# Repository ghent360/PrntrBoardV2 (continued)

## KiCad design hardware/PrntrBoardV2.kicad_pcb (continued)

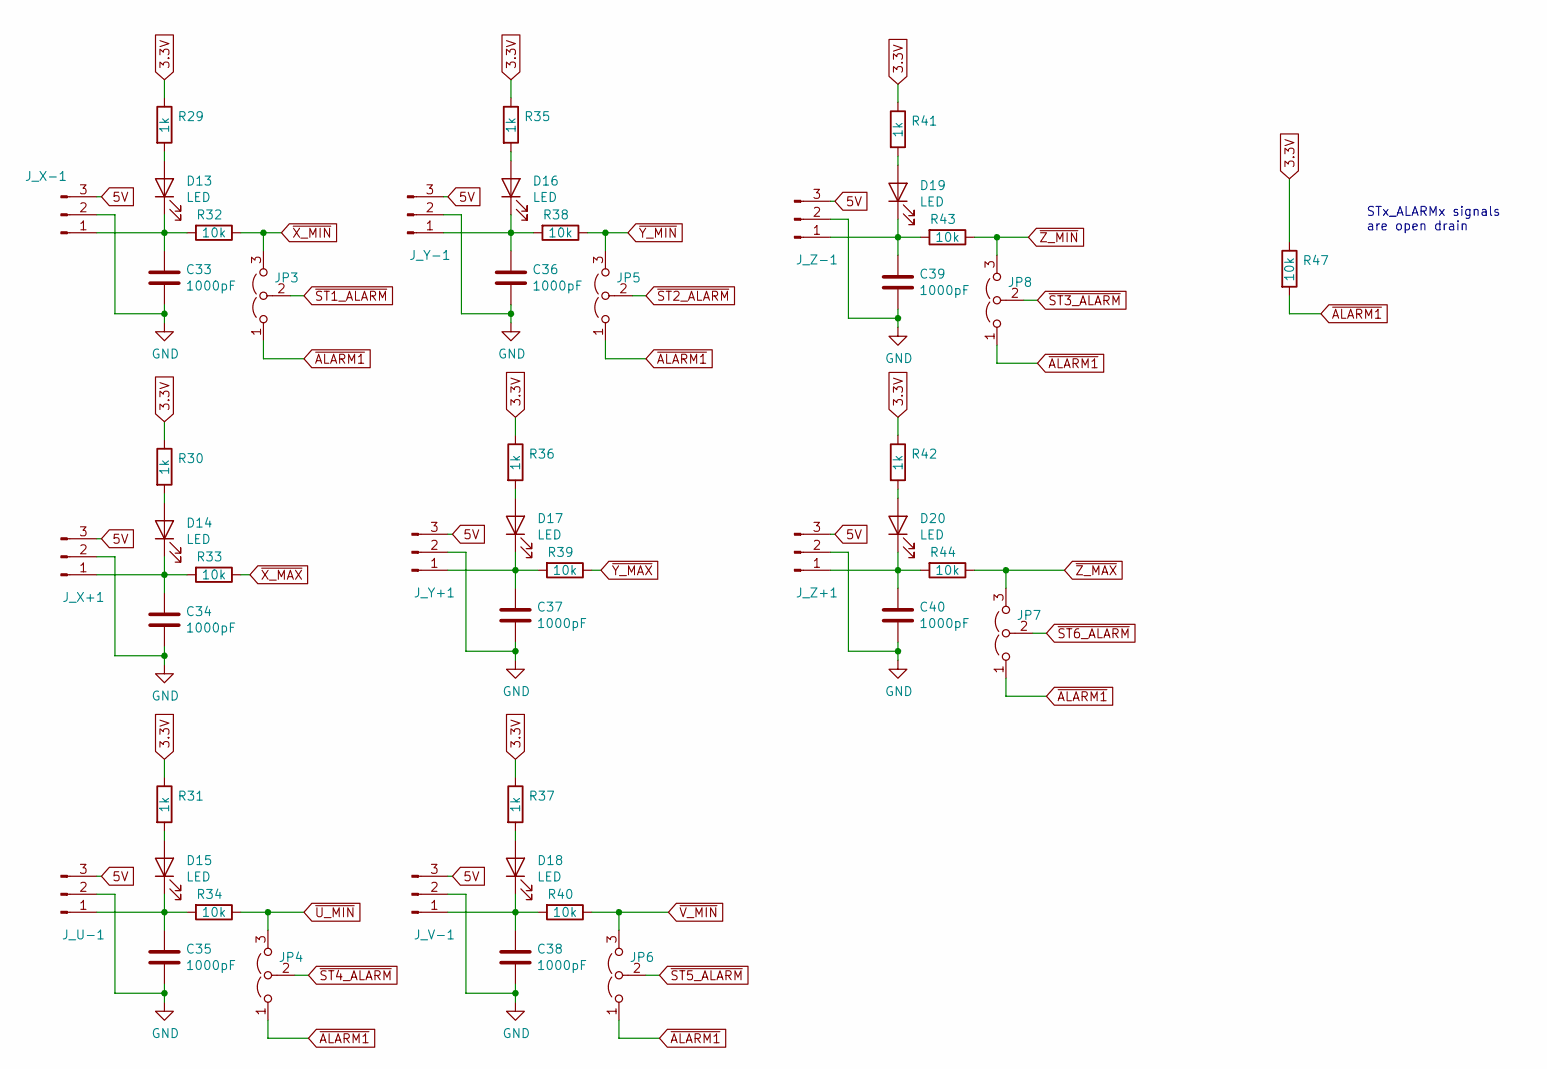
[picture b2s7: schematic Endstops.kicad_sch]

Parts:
C33, C34, C35, C36, C37, C38, C39, C40: 1000pF; C_0603_1608Metric; Part # CL10B102KB8NNNC; LCSC Part # C1588
D13, D14, D15, D16, D17, D18, D19, D20: LED; LED_0603_1608Metric; Part # KT-0603R; LCSC Part # C2286
JP3, JP4, JP5, JP6, JP7, JP8: Jumper_3_Open; PinHeader_1x03_P2.54mm_Vertical; LCSC Part # C152153
J_U-1: JST XH 3p; JST_XH_B3B-XH-A_1x03_P2.50mm_Vertical
J_V-1: JST XH 3p; JST_XH_B3B-XH-A_1x03_P2.50mm_Vertical
J_X+1: JST XH 3p; JST_XH_B3B-XH-A_1x03_P2.50mm_Vertical
J_X-1: JST XH 3p; JST_XH_B3B-XH-A_1x03_P2.50mm_Vertical
J_Y+1: JST XH 3p; JST_XH_B3B-XH-A_1x03_P2.50mm_Vertical
J_Y-1: JST XH 3p; JST_XH_B3B-XH-A_1x03_P2.50mm_Vertical
J_Z+1: JST XH 3p; JST_XH_B3B-XH-A_1x03_P2.50mm_Vertical
J_Z-1: JST XH 3p; JST_XH_B3B-XH-A_1x03_P2.50mm_Vertical
R29, R30, R31, R35, R36, R37, R41, R42: 1k; R_0603_1608Metric; Part # 0603WAF1001T5E; LCSC Part # C21190
R32, R33, R34, R38, R39, R40, R43, R44, R47: 10k; R_0603_1608Metric; Part # 0603WAF1002T5E; LCSC Part # C25804

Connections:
3.3V: R29.1, R30.1, R31.1, R35.1, R36.1, R37.1, R41.1, R42.1, R47.1; also elsewhere on the board
5V: J_U-1.3, J_V-1.3, J_X+1.3, J_X-1.3, J_Y+1.3, J_Y-1.3, J_Z+1.3, J_Z-1.3; also elsewhere on the board
GND: C33.2, C34.2, C35.2, C36.2, C37.2, C38.2, C39.2, C40.2, J_U-1.2, J_V-1.2, J_X+1.2, J_X-1.2, J_Y+1.2, J_Y-1.2, J_Z+1.2, J_Z-1.2; also elsewhere on the board
unnamed: C33.1, D13.1 (K), J_X-1.1, R32.2
unnamed: C34.1, D14.1 (K), J_X+1.1, R33.2
unnamed: C35.1, D15.1 (K), J_U-1.1, R34.2
unnamed: C36.1, D16.1 (K), J_Y-1.1, R38.2
unnamed: C37.1, D17.1 (K), J_Y+1.1, R39.2
unnamed: C38.1, D18.1 (K), J_V-1.1, R40.2
unnamed: C39.1, D19.1 (K), J_Z-1.1, R43.2
unnamed: C40.1, D20.1 (K), J_Z+1.1, R44.2
unnamed: D13.2 (A), R29.2
unnamed: D14.2 (A), R30.2
unnamed: D15.2 (A), R31.2
unnamed: D16.2 (A), R35.2
unnamed: D17.2 (A), R36.2
unnamed: D18.2 (A), R37.2
unnamed: D19.2 (A), R41.2
unnamed: D20.2 (A), R42.2
~ALARM1: JP3.1 (A), JP4.1 (A), JP5.1 (A), JP6.1 (A), JP7.1 (A), JP8.1 (A), R47.2; also elsewhere on the board
~ST1_ALARM: JP3.2 (C); also elsewhere on the board
~ST2_ALARM: JP5.2 (C); also elsewhere on the board
~ST3_ALARM: JP8.2 (C); also elsewhere on the board
~ST4_ALARM: JP4.2 (C); also elsewhere on the board
~ST5_ALARM: JP6.2 (C); also elsewhere on the board
~ST6_ALARM: JP7.2 (C); also elsewhere on the board
~U_MIN: JP4.3 (B), R34.1; also elsewhere on the board
~V_MIN: JP6.3 (B), R40.1; also elsewhere on the board
~X_MAX: R33.1; also elsewhere on the board
~X_MIN: JP3.3 (B), R32.1; also elsewhere on the board
~Y_MAX: R39.1; also elsewhere on the board
~Y_MIN: JP5.3 (B), R38.1; also elsewhere on the board
~Z_MAX: JP7.3 (B), R44.1; also elsewhere on the board
~Z_MIN: JP8.3 (B), R43.1; also elsewhere on the board

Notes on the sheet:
STx_ALARMx signals are open drain

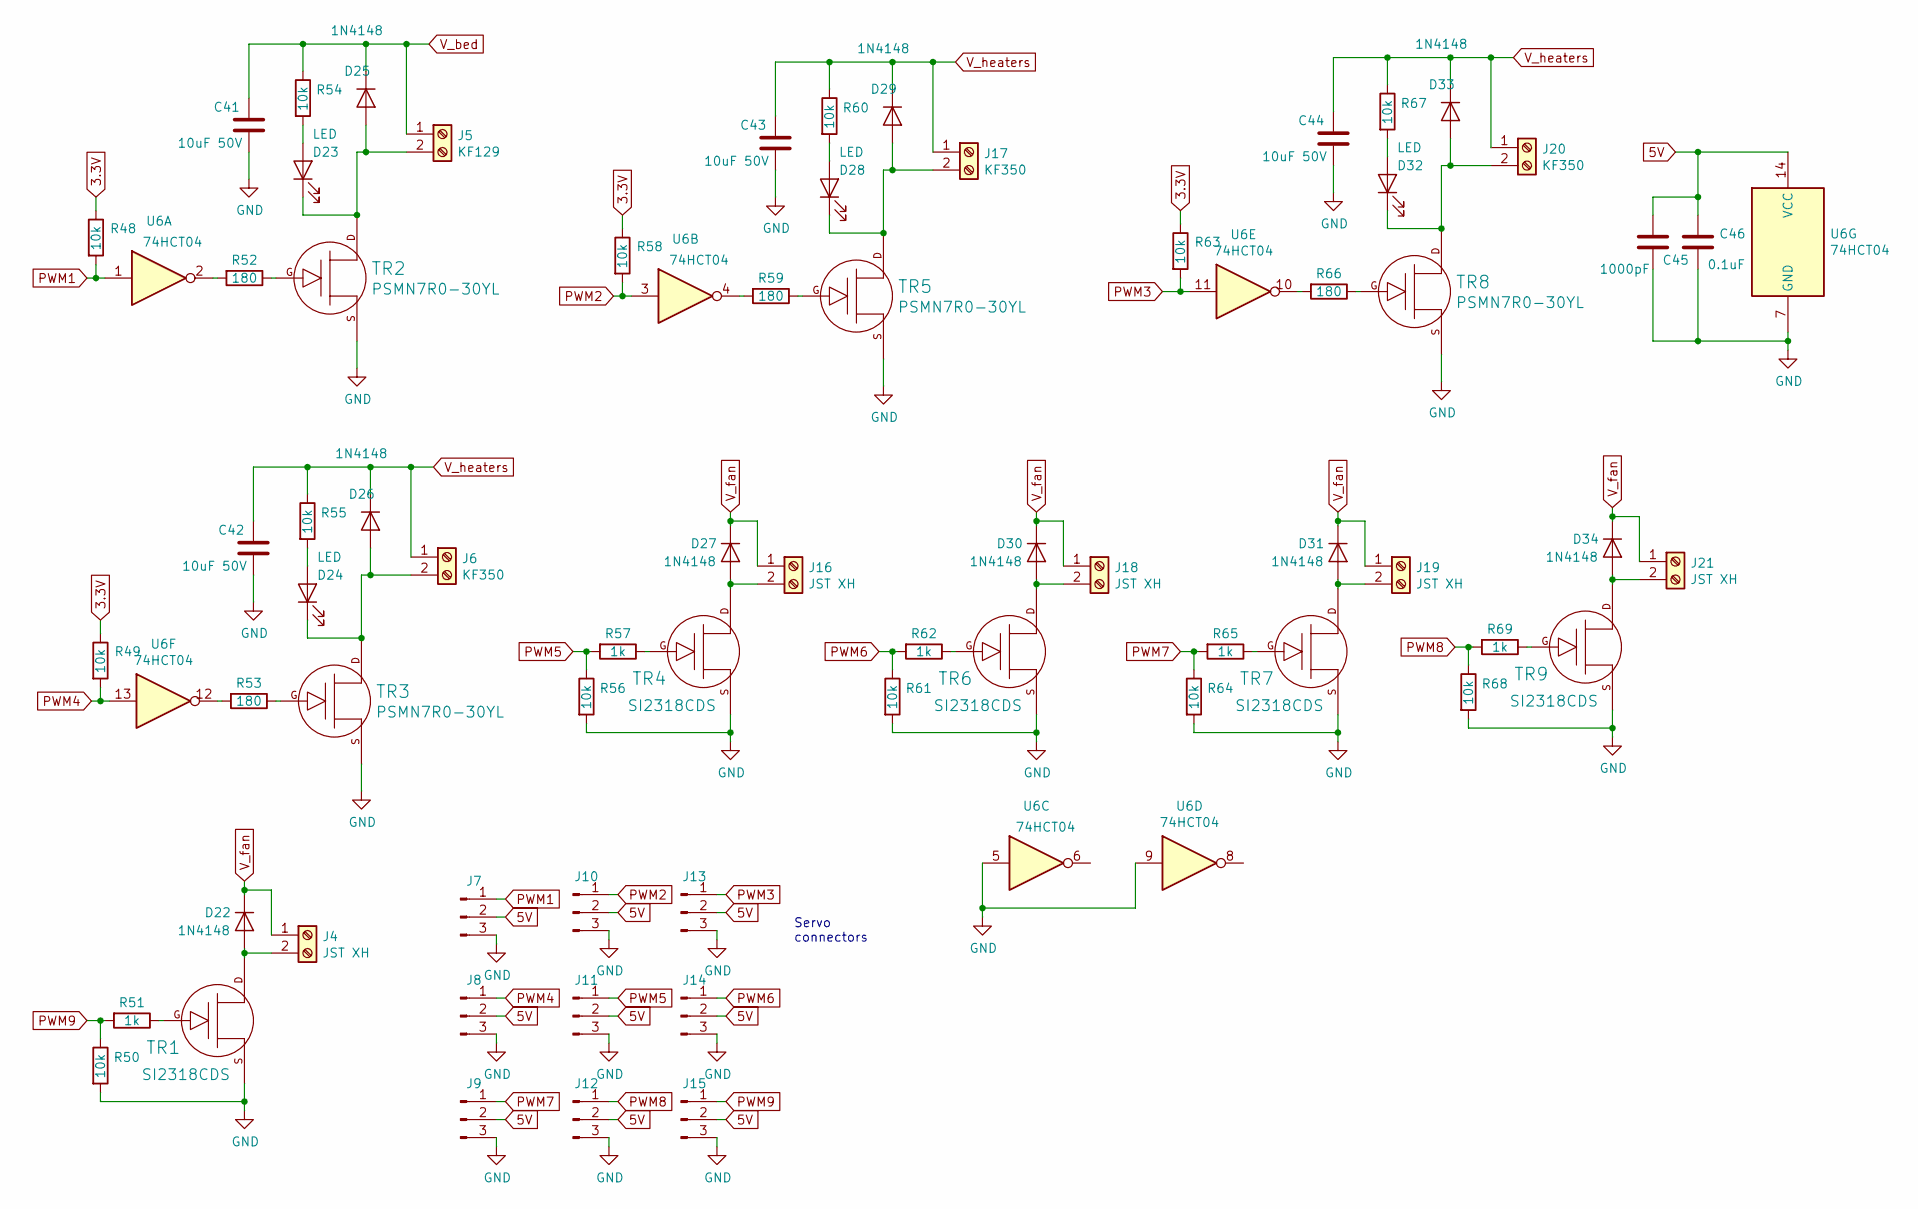
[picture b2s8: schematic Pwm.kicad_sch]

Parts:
C41, C42, C43, C44: 10uF 50V; C_1206_3216Metric; Part # CL31A106KBHNNNE; LCSC Part # C13585
C45: 1000pF; C_0603_1608Metric; Part # CL10B102KB8NNNC; LCSC Part # C1588
C46: 0.1uF; C_0603_1608Metric; Part # CC0603KRX7R9BB104; LCSC Part # C14663
D22, D25, D26, D27, D29, D30, D31, D33, D34: 1N4148; D_SOD-323_HandSoldering; Part # 1N4148WS; LCSC Part # C2128
D23, D24, D28, D32: LED; LED_0603_1608Metric; Part # KT-0603R; LCSC Part # C2286
J4, J16, J18, J19, J21: JST XH; JST_XH_B2B-XH-A_1x02_P2.50mm_Vertical
J5: KF129; TerminalBlock_Phoenix_MKDS-1,5-2-5.08_1x02_P5.08mm_Horizont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
J6, J17, J20: KF350; TerminalBlock_Phoenix_PT-1,5-2-3.5-H_1x02_P3.50mm_Horizontal
J7, J8, J9, J10, J11, J12, J13, J14, J15: Conn_01x03_Male; PinHeader_1x03_P2.54mm_Vertical
R48, R49, R50, R54, R55, R56, R58, R60, R61, R63, R64, R67, R68: 10k; R_0603_1608Metric; Part # 0603WAF1002T5E; LCSC Part # C25804
R51, R57, R62, R65, R69: 1k; R_0603_1608Metric; Part # 0603WAF1001T5E; LCSC Part # C21190
R52, R53, R59, R66: 180; R_0603_1608Metric; Part # 0603WAF1800T5E; LCSC Part # C22828
TR1, TR4, TR6, TR7, TR9: SI2318CDS; SOT-23; Part # AO3400A; LCSC Part # C20917
TR2, TR3, TR5, TR8: PSMN7R0-30YL; SOT-669_LFPAK; Part # PSMN1R5-30YLC; LCSC Part # C427523
U6: 74HCT04; TSSOP-14_4.4x5mm_P0.65mm; Part # 74HCT04PW,118; LCSC Part # C131317

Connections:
3.3V: R48.1, R49.1, R58.1, R63.1; also elsewhere on the board
5V: C45.1, C46.1, J7.2, J8.2, J9.2, J10.2, J11.2, J12.2, J13.2, J14.2, J15.2, U6.14 (VCC); also elsewhere on the board
GND: C41.2, C42.2, C43.2, C44.2, C45.2, C46.2, J7.3, J8.3, J9.3, J10.3, J11.3, J12.3, J13.3, J14.3, J15.3, R50.2, R56.2, R61.2, R64.2, R68.2, TR1.S, TR2.S, TR3.S, TR4.S, TR5.S, TR6.S, TR7.S, TR8.S, TR9.S, U6.5, U6.7 (GND), U6.9; also elsewhere on the board
unnamed: D22.2 (A), J4.2, TR1.D
unnamed: D23.1 (K), D25.2 (A), J5.2, TR2.D
unnamed: D23.2 (A), R54.2
unnamed: D24.1 (K), D26.2 (A), J6.2, TR3.D
unnamed: D24.2 (A), R55.2
unnamed: D27.2 (A), J16.2, TR4.D
unnamed: D28.1 (K), D29.2 (A), J17.2, TR5.D
unnamed: D28.2 (A), R60.2
unnamed: D30.2 (A), J18.2, TR6.D
unnamed: D31.2 (A), J19.2, TR7.D
unnamed: D32.1 (K), D33.2 (A), J20.2, TR8.D
unnamed: D32.2 (A), R67.2
unnamed: D34.2 (A), J21.2, TR9.D
unnamed: R51.1, TR1.G
unnamed: R52.1, TR2.G
unnamed: R52.2, U6.2
unnamed: R53.1, TR3.G
unnamed: R53.2, U6.12
unnamed: R57.1, TR4.G
unnamed: R59.1, TR5.G
unnamed: R59.2, U6.4
unnamed: R62.1, TR6.G
unnamed: R65.1, TR7.G
unnamed: R66.1, TR8.G
unnamed: R66.2, U6.10
unnamed: R69.1, TR9.G
PWM1: J7.1, R48.2, U6.1; also elsewhere on the board
PWM2: J10.1, R58.2, U6.3; also elsewhere on the board
PWM3: J13.1, R63.2, U6.11; also elsewhere on the board
PWM4: J8.1, R49.2, U6.13; also elsewhere on the board
PWM5: J11.1, R56.1, R57.2; also elsewhere on the board
PWM6: J14.1, R61.1, R62.2; also elsewhere on the board
PWM7: J9.1, R64.1, R65.2; also elsewhere on the board
PWM8: J12.1, R68.1, R69.2; also elsewhere on the board
PWM9: J15.1, R50.1, R51.2; also elsewhere on the board
V_bed: C41.1, D25.1 (K), J5.1, R54.1; also elsewhere on the board
V_fan: D22.1 (K), D27.1 (K), D30.1 (K), D31.1 (K), D34.1 (K), J4.1, J16.1, J18.1, J19.1, J21.1; also elsewhere on the board
V_heaters: C42.1, C43.1, C44.1, D26.1 (K), D29.1 (K), D33.1 (K), J6.1, J17.1, J20.1, R55.1, R60.1, R67.1; also elsewhere on the board

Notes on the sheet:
Servo connectors

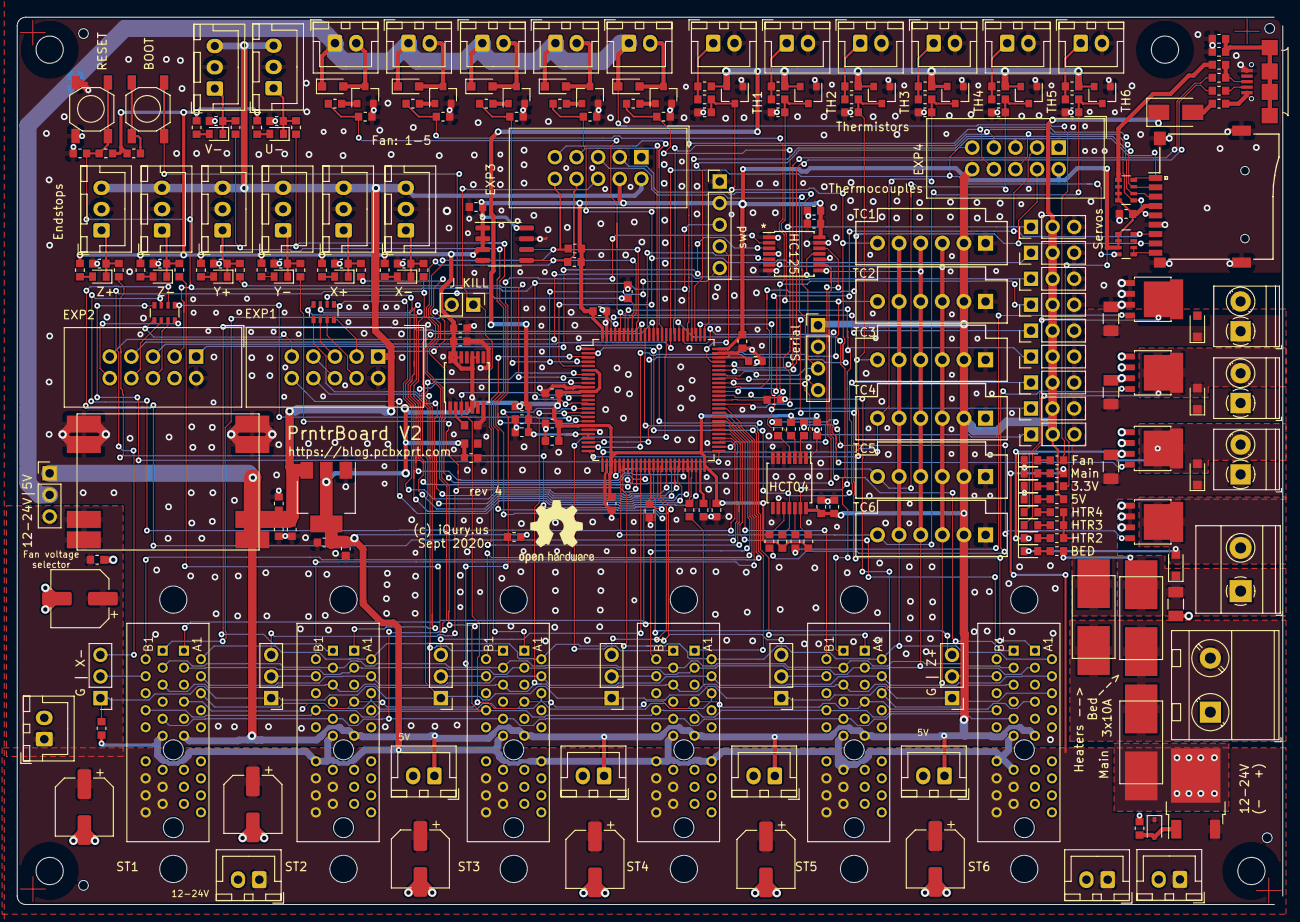
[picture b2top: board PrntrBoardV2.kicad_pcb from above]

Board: 2 copper layers, 148.7 x 104.3 mm, 266 parts (0 on the bottom side), 177 nets.

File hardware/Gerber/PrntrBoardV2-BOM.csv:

Comment,Designator,Footprint,LCSC, LCSC Part #, Part #
"10uF","C20,C23,C26,C56,C2,C5,C6,C15","PrntrBoardV2:C_0603_1608Metric","","C19702","CL10A106KP8NNNC"
"0.1uF","C21,C22,C57,C18,C19,C54,C1,C4,C7,C8,C9,C10,C11,C12,C13,C14,C17,C53,C46","PrntrBoardV2:C_0603_1608Metric","","C14663","CC0603KRX7R9BB104"
"0.1uF 50V","C24","PrntrBoardV2:C_0603_1608Metric","","C14663","CL05B104KO5NNNCC0603KRX7R9BB104C"
"100uF 35V","C25,C47,C48,C49,C50,C51,C52","Capacitor_SMD:CP_Elec_6.3x7.7","","C134792","VES101M1VTR-0607"
"1000pF","C27,C28,C29,C30,C31,C32,C33,C34,C35,C36,C37,C38,C39,C40,C3,C16,C45","PrntrBoardV2:C_0603_1608Metric","","C1588","CL10B102KB8NNNC"
"10uF 50V","C41,C42,C43,C44","PrntrBoardV2:C_1206_3216Metric","","C13585","CL31A106KBHNNNE"
"B5819W","D1,D21,D22,D25,D26,D27,D29,D30,D31,D33","Diode_SMD:D_SOD-123",""," C8598","B5819W"
"LED","D2,D3,D4,D5,D13,D14,D15,D16,D17,D18,D19,D20,D23,D24,D28,D32","PrntrBoardV2:LED_0603_1608Metric","","C2286","KT-0603R"
"10V","D6","Diode_SMD:D_SOD-323","","C131828","LM3Z10VT1G"
"BAT54S","D7,D8,D9,D10,D11,D12","Package_TO_SOT_SMD:SOT-23","","C181201","BAT54S"
"IDC 2x5","EXP1,EXP2,EXP3","Connector_IDC:IDC-Header_2x05_P2.54mm_Vertical","","C5661",""
"500mA","F1","PrntrBoardV2:R_0603_1608Metric","","C261937","TLC-FSMD050"
"Fuse","F2,F3,F4","PrntrBoardV2:2410_FuseFolder",""
"600 ohm @ 100MHz","FB1","Inductor_SMD:L_0805_2012Metric","","C1017","GZ2012D601TF"
"JST XH","J1,J2,J22,J23,J24,J25,J26,J27,J_TH1,J_TH2,J_TH3,J_TH4,J_TH5,J_TH6,J4,J16,J18,J19,J21","Connector_JST:JST_XH_B2B-XH-A_1x02_P2.50mm_Vertical",""
"KF350","J28,J6,J17,J20","PrntrBoardV2:TerminalBlock_Phoenix_PT-1,5-2-3.5-H_1x02_P3.50mm_Horizontal",""
"RJ12_Shielded","J29","Connector_RJ:RJ12_Amphenol_54601",""
"USB_B_Micro","J3","PrntrBoardV2:MC-101C","","C183609","SOFNG MC-101C"
"KF129","J5","PrntrBoardV2:TerminalBlock_Phoenix_MKDS-1,5-2-5.08_1x02_P5.08mm_Horizontal",""
"Conn_01x03_Male","J7,J8,J9,J10,J11,J12,J13,J14,J15","Connector_PinHeader_2.54mm:PinHeader_1x03_P2.54mm_Vertical",""
"Jumper_2_Open","JP1","Connector_PinHeader_2.54mm:PinHeader_1x02_P2.54mm_Vertical","","C160332",""
"Jumper_3_Open","JP2,JP3,JP4,JP5,JP6,JP7,JP8","Connector_PinHeader_2.54mm:PinHeader_1x03_P2.54mm_Vertical","","C152153",""
"Serial 0","J_SER1","Connector_PinHeader_2.54mm:PinHeader_1x04_P2.54mm_Vertical","","C358686",""
"PCIe_Stepper","J_ST1,J_ST2,J_ST3,J_ST4,J_ST5,J_ST6","PrntrBoardV2:AMPHENOL_10018784-10210TLF",""
"SWD","J_SWD1","Connector_PinHeader_2.54mm:PinHeader_1x05_P2.54mm_Vertical",""
"JST XH 3p","J_U-1,J_V-1,J_X+1,J_X-1,J_Y+1,J_Y-1,J_Z+1,J_Z-1","Connector_JST:JST_XH_B3B-XH-A_1x03_P2.50mm_Vertical",""
"KF635","J_power_in1","TerminalBlock_MetzConnect:TerminalBlock_MetzConnect_Type701_RT11L02HGLU_1x02_P6.35mm_Horizontal",""
"Net-Tie_2","NT1","NetTie:NetTie-2_SMD_Pad0.5mm",""
"NCE40P40K","Q1","Package_TO_SOT_SMD:TO-252-2","","C130100","NCE40P40K"
"22","R10,R11,R72","PrntrBoardV2:R_0603_1608Metric","","C23345","0603WAF220JT5E"
"10k","R13,R14,R19,R20,R23,R24,R27,R28,R2,R73,R77,R78,R32,R33,R34,R38,R39,R40,R43,R44,R47,R1,R3,R5,R6,R7,R70,R48,R49,R50,R54,R55,R56,R58,R60,R61,R63,R64,R67,R68","PrntrBoardV2:R_0603_1608Metric","","C25804","0603WAF1002T5E"
"470","R15,R45,R46","PrntrBoardV2:R_0603_1608Metric","","C23179","0603WAF4700T5E"
"1k","R16,R29,R30,R31,R35,R36,R37,R41,R42,R8,R51,R57,R62,R65,R69","PrntrBoardV2:R_0603_1608Metric","","C21190","0603WAF1001T5E"
"4k7","R17,R18,R21,R22,R25,R26","PrntrBoardV2:R_0603_1608Metric","","C23162","0603WAF4701T5E"
"180","R52,R53,R59,R66","PrntrBoardV2:R_0603_1608Metric","","C22828","0603WAF1800T5E"
"100k","R71,R12","PrntrBoardV2:R_0603_1608Metric","","C25803","0603WAF1003T5E"
"56","R74,R75","PrntrBoardV2:R_0603_1608Metric","","C25196","0603WAF560JT5E"
"1.5k","R9","PrntrBoardV2:R_0603_1608Metric","","C22843","0603WAF1501T5E"
"4x470","RN1,RN2","Resistor_SMD:R_Array_Convex_4x0603","","C25510","4D03WGJ0471T5E"
"4x10k","RN3","Resistor_SMD:R_Array_Convex_4x0603","","C29718","4D03WGJ0103T5E"
"SW_Push","SW_BOOT1,SW_RST1","PrntrBoardV2:Button_4x4","","C318884","TS-1187A-B-A-B"
"TC","TC1,TC2,TC3,TC4,TC5,TC6","kicad-molex-sl-footprints:Molex-SL-6POS",""
"SI2318CDS","TR1,TR4,TR6,TR7,TR9","PrntrBoardV2:SOT-23","","C20917","AO3400A"
"PSMN7R0-30YL","TR2,TR3,TR5,TR8","PrntrBoardV2:SOT-669_LFPAK","","C427523","PSMN1R5-30YLC"
"74LVC125","U1,U7","Package_SO:TSSOP-14_4.4x5mm_P0.65mm","","C6059","74LVC125APW,118"
"STM32F407VETx","U2","Package_QFP:LQFP-100_14x14mm_P0.5mm","","C28730","STM32F407VET6"
"24LC64","U3","Package_SO:SO-8_3.9x4.9mm_P1.27mm","","C5460","24LC64T-I/SN"
"AMS1117-3.3","U4","Package_TO_SOT_SMD:SOT-223-3_TabPin2","","C6186","AMS1117-3.3"
"74HCT04","U6","Package_SO:TSSOP-14_4.4x5mm_P0.65mm","","C131317","74HCT04PW,118"
"TJA1040","U8","Package_SO:SOIC-8_3.9x4.9mm_P1.27mm","","C6951","TJA1040T/CM,118"
"12MHz","X1","Oscillator:Oscillator_SMD_EuroQuartz_XO32-4Pin_3.2x2.5mm","","C29752","SIT1602AI-22-33E-12.000000D"
"MicroSD","XS1","PrntrBoardV2:Conn_uSDcard","","C111196","SOFNG TF-15×15"

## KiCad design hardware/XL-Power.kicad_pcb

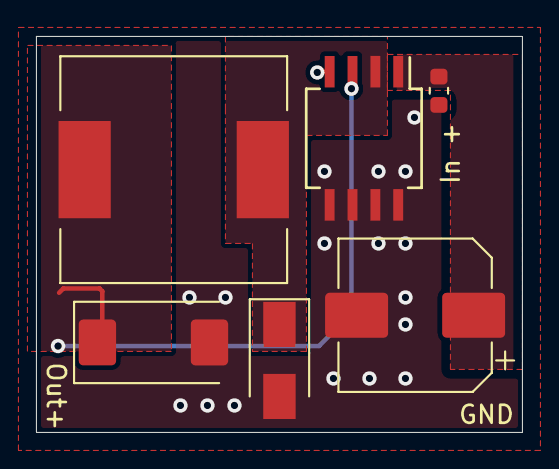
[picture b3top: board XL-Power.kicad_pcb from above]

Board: 2 copper layers, 27.0 x 22.0 mm, 6 parts (0 on the bottom side), 4 nets.

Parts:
C1: 470uF 35V; CP_Elec_8x10
C2: 0.1uF 50V; C_0603_1608Metric
C3: 220uF; CP_EIA-7343-31_Kemet-D
D1: SS34; D_SMA
L1: 68uH 2.1A; L_12x12mm_H8mm
U1: XL1509-5.0E1; SO-8_5.3x6.2mm_P1.27mm

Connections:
/5V: C3.1, L1.2, U1.3
/Vin: C1.1, C2.1, U1.1
GND: C1.2, C2.2, C3.2, D1.2, U1.4, U1.5, U1.6, U1.7, U1.8
unnamed: D1.1, L1.1, U1.2
